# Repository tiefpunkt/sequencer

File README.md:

# Sequencer

* 0-5V (or almost) CV & Gate
* 5-8 steps
* Incl. clock source
* Clock in & out allow running multiple sequencers on the same clock source

## License
This work is licensed under the Creative Commons Attribution-ShareAlike 4.0 International License. To view a copy of this license, visit http://creativecommons.org/licenses/by-sa/4.0/.

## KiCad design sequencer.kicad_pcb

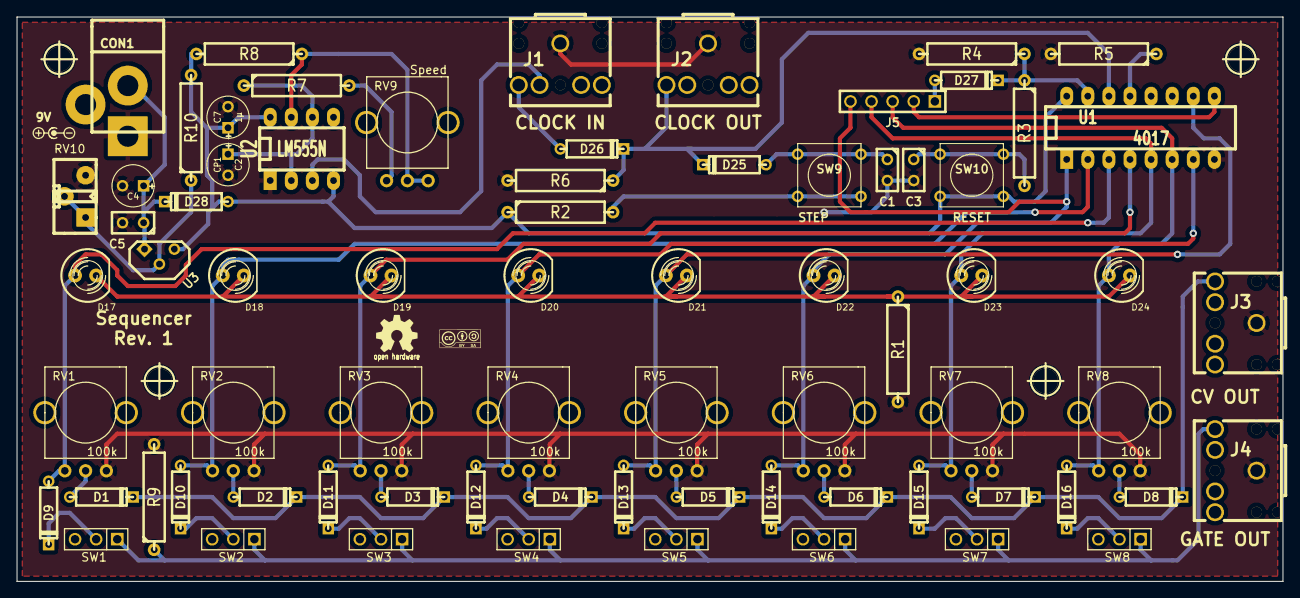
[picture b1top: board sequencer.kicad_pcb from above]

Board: 2 copper layers, 152.4 x 67.9 mm, 77 parts (0 on the bottom side), 44 nets.

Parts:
C1, C3: C; C1
C2: CP1; C1V5
C4: 10µ; C1V5
C5: 100n; C1
C7: 1µ; C1V5
CON1: 9V; JACK_ALIM_ROUND
D1, D2, D3, D4, D5, D6, D7, D8, D9, D10, D11, D12, D13, D14, D15, D16, D25, D26, D27: 1N4148; D3
D17, D18, D19, D20, D21, D22, D23, D24: LED; LED-5MM
D28: 1N4002; D3
J1: CLOCK IN; AudioJack3.5mm
J2: CLOCK OUT; AudioJack3.5mm
J3: CV OUT; AudioJack3.5mm
J4: GATE OUT; AudioJack3.5mm
J5: HEADER_5; PIN_ARRAY_5x1
R1: 220; R5
R2, R3: 10k; R5
R4, R5, R6, R9: 47k; R5
R7, R8: 1k; R5
R10: 240; R5
RV1, RV2, RV3, RV4, RV5, RV6, RV7, RV8: 100k; RV09
RV9: Speed; RV09
RV10: 5k; POACAV
SW1, SW2, SW3, SW4, SW5, SW6, SW7, SW8: SPST; PIN_ARRAY_3X1
SW9: STEP; SW_PUSH_SMALL
SW10: RESET; SW_PUSH_SMALL
U1: 4017; DIP-16__300_ELL
U2: LM555N; DIP-8__300_ELL
U3: LM317; TO92
hole_3mm, hole_3mm#2, hole_3mm#3, hole_3mm#4: VAL**; hole_3mm

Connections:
GND: C1.2, C2.2, C3.2, C4.2, C5.2, C7.2, CON1.1, J1.1, J2.1, J3.1, J4.1, R1.2, R4.2, R5.2, R6.2, R9.2, RV1.3, RV2.3, RV3.3, RV4.3, RV5.3, RV6.3, RV7.3, RV8.3, RV10.3, U1.8, U2.1
unnamed: D27.2, R3.1, R4.1, U1.15
unnamed: R5.1, U1.13
unnamed: D17.2, D18.2, D19.2, D20.2, D21.2, D22.2, D23.2, D24.2, R1.1
unnamed: J1.4, U2.3
unnamed: D26.1, J1.2
unnamed: C1.1, D25.1, SW9.1
unnamed: D25.2, D26.2, J2.2, R6.1, U1.14
unnamed: R2.2, SW9.2
unnamed: J4.2, R9.1, SW1.1, SW2.1, SW3.1, SW4.1, SW5.1, SW6.1, SW7.1, SW8.1
unnamed: D9.1, D17.1, RV1.1, U1.3
unnamed: R10.1, RV10.1, RV10.2, U3.2
unnamed: D27.1, J5.1
unnamed: J5.2, U1.9
unnamed: D1.2, D2.2, D3.2, D4.2, D5.2, D6.2, D7.2, D8.2, J3.2
unnamed: C2.1, R7.1, U2.2, U2.6
unnamed: R7.2, RV9.1
unnamed: R8.1, RV9.2, RV9.3, U2.7
unnamed: C3.1, R3.2, SW10.1
unnamed: C4.1, C5.1, CON1.2, D28.2, U3.1
unnamed: D6.1, RV6.2
unnamed: D7.1, RV7.2
unnamed: D8.1, RV8.2
unnamed: D4.1, RV4.2
unnamed: D3.1, RV3.2
unnamed: D2.1, RV2.2
unnamed: D1.1, RV1.2
unnamed: D5.1, RV5.2
unnamed: D13.1, D21.1, RV5.1, U1.10
unnamed: D16.2, SW8.2
unnamed: D15.2, SW7.2
unnamed: D14.2, SW6.2
unnamed: D13.2, SW5.2
unnamed: D12.2, SW4.2
unnamed: D11.2, SW3.2
unnamed: D10.2, SW2.2
unnamed: D9.2, SW1.2
unnamed: D15.1, D23.1, J5.4, RV7.1, U1.5
unnamed: D14.1, D22.1, J5.5, RV6.1, U1.1
unnamed: D11.1, D19.1, RV3.1, U1.4
unnamed: D10.1, D18.1, RV2.1, U1.2
unnamed: D16.1, D24.1, J5.3, RV8.1, U1.6
unnamed: D12.1, D20.1, RV4.1, U1.7
VCC: C7.1, D28.1, R2.1, R8.2, R10.2, SW10.2, U1.16, U2.4, U2.8, U3.3
